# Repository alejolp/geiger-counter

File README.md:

# Geiger Counter with MC34063

See schematic.png

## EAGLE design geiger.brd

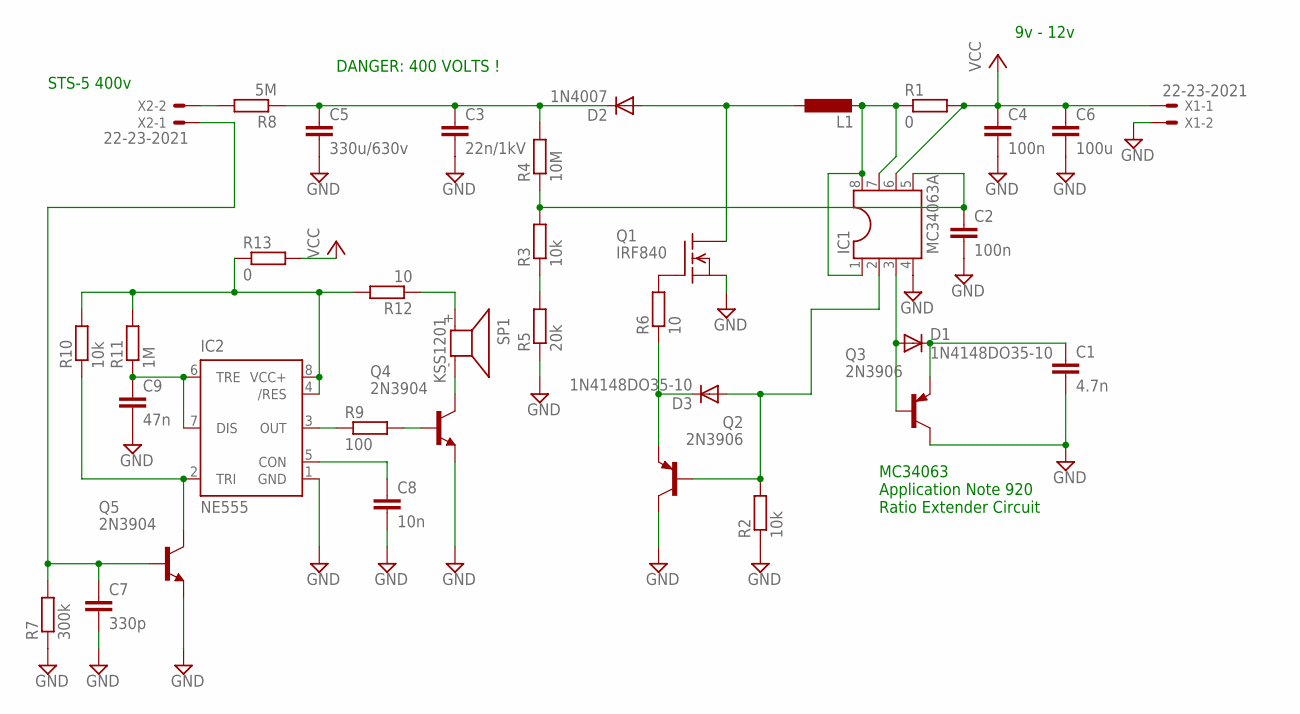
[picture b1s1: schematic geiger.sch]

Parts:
C1: 4.7n; C025-025X050
C2, C4: 100n; C025-025X050
C3: 22n/1kV; C050-050X075
C5: 330u/630v; C050-050X075
C6: 100u; C025-025X050
C7: 330p; C025-025X050
C8: 10n; C025-025X050
C9: 47n; C025-025X050
D1, D3: 1N4148DO35-10; DO35-10
D2: 1N4007; D-7.5
IC1: MC34063A; DIL08
IC2: NE555; DIL-08
L1: L-EU0207/12; 0207/12
Q1: IRF840; TO220
Q2, Q3: 2N3906; TO92
Q4, Q5: 2N3904; TO92
R1, R13: 0; 0204/7
R2, R3, R10: 10k; 0204/7
R4: 10M; 0204/7
R5: 20k; 0204/7
R6, R12: 10; 0204/7
R7: 300k; 0204/7
R8: 5M; 0204/7
R9: 100; 0204/7
R11: 1M; 0204/7
SP1: KSS1201
X1, X2: 22-23-2021

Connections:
GND: C1.2, C2.2, C3.2, C4.2, C5.2, C6.2, C7.2, C8.2, C9.2, IC1.4, IC2.1 (GND), Q1.3 (S), Q2.1 (C), Q3.1 (C), Q4.3 (E), Q5.3 (E), R2.1, R5.1, R7.1, X1.2
unnamed: D1.A, IC1.3, Q3.2 (B)
unnamed: C1.1, D1.C, Q3.3 (E)
unnamed: D2.A, L1.1, Q1.2 (D)
unnamed: R3.1, R5.2
unnamed: IC1.1, IC1.7, IC1.8, L1.2, R1.1
unnamed: D3.C, Q2.3 (E), R6.1
unnamed: IC2.4 (/RES), IC2.8 (VCC+), R10.2, R11.2, R12.2, R13.1
unnamed: C3.1, C5.1, D2.C, R4.2, R8.1
unnamed: Q1.1 (G), R6.2
unnamed: C7.1, Q5.2 (B), R7.2, X2.1
unnamed: D3.A, IC1.2, Q2.2 (B), R2.2
unnamed: R8.2, X2.2
unnamed: IC2.2 (TRI), Q5.1 (C), R10.1
unnamed: C8.1, IC2.5 (CON)
unnamed: IC2.3 (OUT), R9.1
unnamed: Q4.2 (B), R9.2
unnamed: Q4.1 (C), SP1.- (2)
unnamed: C9.1, IC2.6 (TRE), IC2.7 (DIS), R11.1
unnamed: R12.1, SP1.+ (1)
unnamed: C2.1, IC1.5, R3.2, R4.1
VCC: C4.1, C6.1, IC1.6, R1.2, R13.2, X1.1

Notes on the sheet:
MC34063 Application Note 920 Ratio Extender Circuit
STS-5 400v
9v - 12v
DANGER: 400 VOLTS !

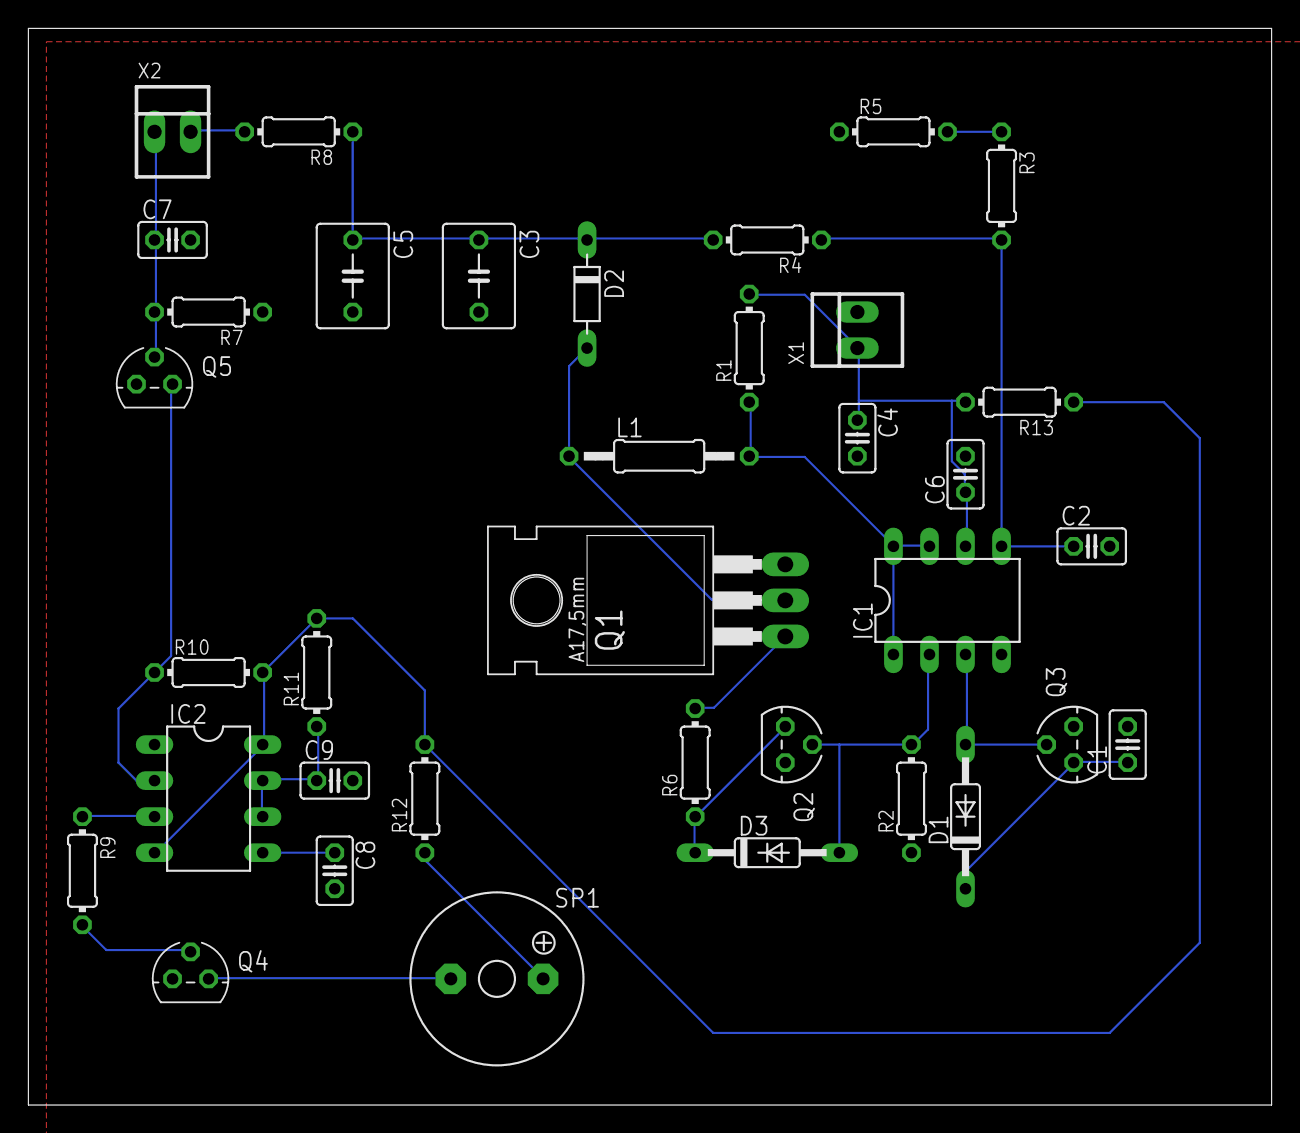
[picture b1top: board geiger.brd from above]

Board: 2 copper layers, 87.6 x 75.9 mm, 36 parts (0 on the bottom side), 22 nets.

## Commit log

2017-09-07 First version, power supply only
2017-09-07 fixes
2017-09-10 beeping
2017-09-10 schematic
